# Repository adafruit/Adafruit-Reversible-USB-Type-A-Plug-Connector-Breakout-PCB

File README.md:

## Adafruit Reversible USB Type A Plug Connector Breakout PCB

<a href="http://www.adafruit.com/products/6001"><br/>
Click here to purchase one from the Adafruit shop</a>

PCB files for the Adafruit Reversible USB Type A Plug Connector Breakout. 

Format is EagleCAD schematic and board layout
* https://www.adafruit.com/product/6001

### Description

Quantum superposition is a physics concept that light and matter can be both particle and wave at the same time. This amazing phenomenon can be demonstrated at home when you try to plug in a USB Type A cable in, it's both right-side-up and upside-down at the same time! That's why you have to try at least 3 times to plug it in.

The Adafruit Reversible USB Type A Plug Connector Breakout solves this issue by having a thin contact piece in the middle, so you can plug it either way and it always has the same pin-out. Great for boards with indicator LEDs or displays that need to be facing 'up' or 'out' no matter which way the port is setup.

The connector we use is half through-hole and half-SMT, so there's a good mechanical connection to the PCB via mounting tabs. You get all four classic USB connectors (5V, ground, D+ and D-) plus a 'shield' contact for the metal body. We also toss in a small bit of header in case you want to use this in a perf or bread board.

### License

Adafruit invests time and resources providing this open source design, please support Adafruit and open-source hardware by purchasing products from [Adafruit](https://www.adafruit.com)!

Designed by Limor Fried/Ladyada for Adafruit Industries.

Creative Commons Attribution/Share-Alike, all text above must be included in any redistribution. 
See license.txt for additional details.

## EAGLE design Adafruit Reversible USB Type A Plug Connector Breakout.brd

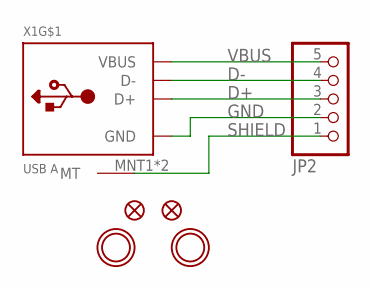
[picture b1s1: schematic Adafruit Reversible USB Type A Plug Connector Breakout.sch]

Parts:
FID1, FID2: FIDUCIAL_0.5MM
JP2: HEADER-1X570MIL; 1X05_ROUND_70
U$1, U$2: MOUNTINGHOLE2.5; MOUNTINGHOLE_2.5_PLATED
X1: USB A; USB_A-UG08WSW01

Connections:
D+: JP2.3, X1.D+
D-: JP2.4, X1.D-
GND: JP2.2, X1.GND
SHIELD: JP2.1, X1.MNT1 (MT), X1.MNT2 (MT)
VBUS: JP2.5, X1.VBUS

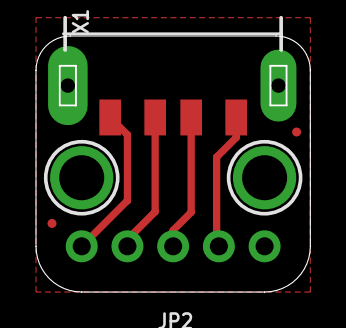
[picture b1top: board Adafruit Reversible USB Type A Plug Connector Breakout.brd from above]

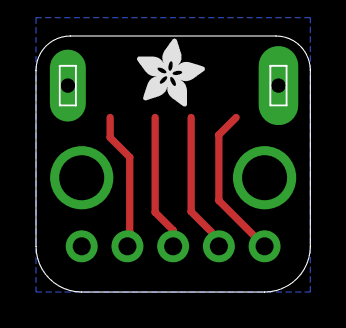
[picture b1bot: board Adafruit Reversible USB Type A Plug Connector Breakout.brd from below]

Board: 2 copper layers, 15.1 x 14.1 mm, 14 parts (2 on the bottom side), 5 nets.

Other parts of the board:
PLABEL0: PLABEL0
PLABEL1: PLABEL1
PLABEL2: PLABEL2
PLABEL3: PLABEL3
PLABEL4: PLABEL4
PLABEL5: PLABEL5
PLABEL6: PLABEL6
U$4: ADAFRUIT_3.5MM

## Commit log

2024-08-12 cookiecutter

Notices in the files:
parts and their libraries:
microbuilder: This work is placed in the public domain, and may be freely used for commercial and non-commercial work with the following conditions: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
